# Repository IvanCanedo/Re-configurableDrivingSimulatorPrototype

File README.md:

# Re-configurableDrivingSimulatorPrototype
All files for a Re-configurable Driving Simulator Prototype

Requirements:

Windows 10 20H2

Solidworks Premium 2019 SP4.0

MATLAB 2018b 9.5.0.944444

LabVIEW 2019 19.0f2

KiCad 5.1.10

-To run MATLAB/Simulink simulation-

First open and run

/MATLAB/cinematica_inversa.m

then open and run:

/MATLAB/simulacion/platafomra_esfera.slx

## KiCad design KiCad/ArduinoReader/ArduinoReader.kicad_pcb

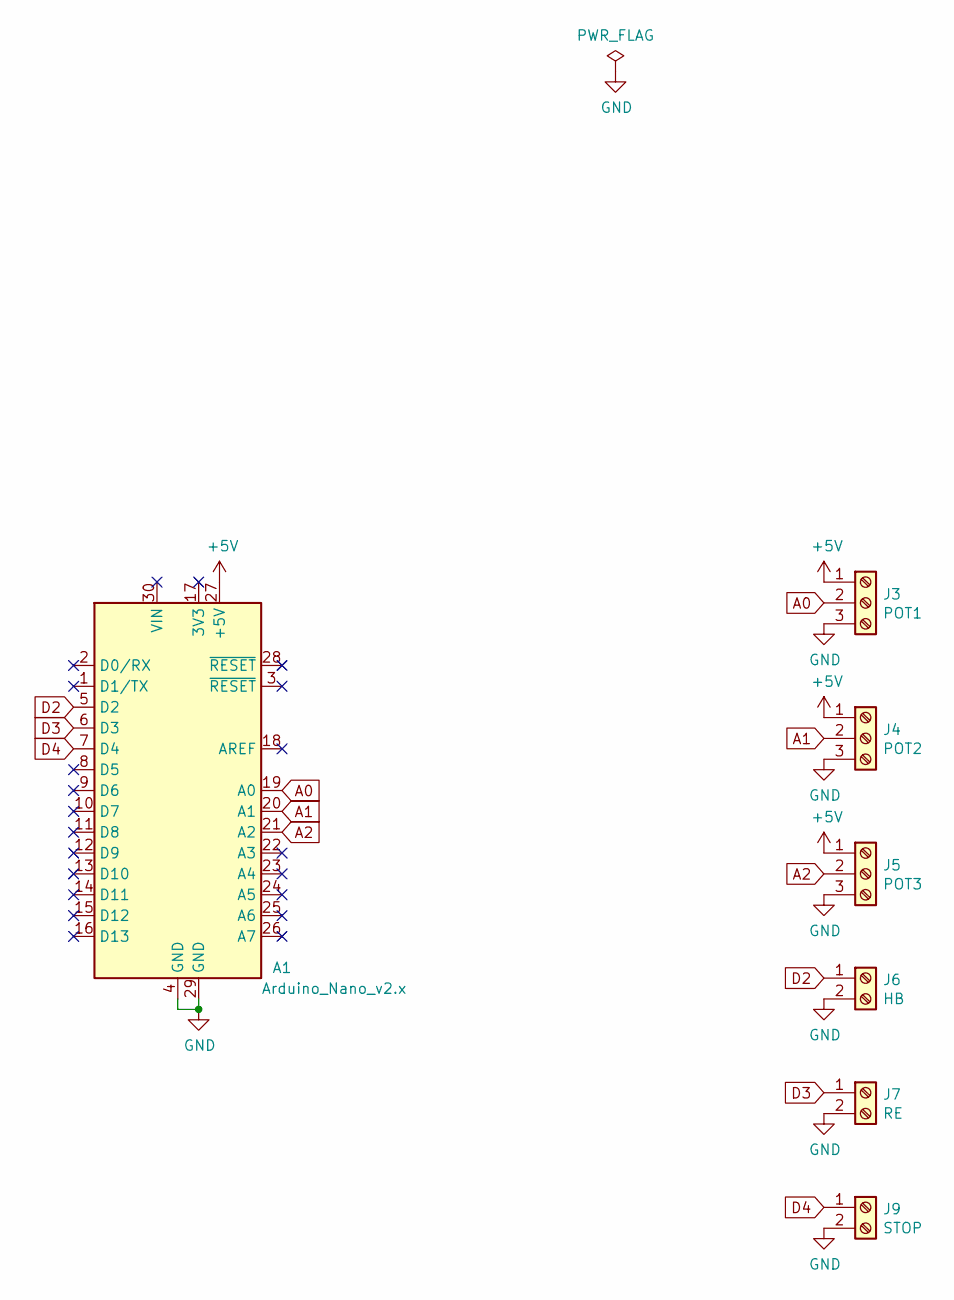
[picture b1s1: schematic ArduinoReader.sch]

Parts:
A1: Arduino_Nano_v2.x; Arduino_Nano
J3: POT1; TerminalBlock_Phoenix_MKDS-1,5-3_1x03_P5.00mm_Horizontal
J4: POT2; TerminalBlock_Phoenix_MKDS-1,5-3_1x03_P5.00mm_Horizontal
J5: POT3; TerminalBlock_Phoenix_MKDS-1,5-3_1x03_P5.00mm_Horizontal
J6: HB; TerminalBlock_Phoenix_MKDS-1,5-2_1x02_P5.00mm_Horizontal
J7: RE; TerminalBlock_Phoenix_MKDS-1,5-2_1x02_P5.00mm_Horizontal
J9: STOP; TerminalBlock_Phoenix_MKDS-1,5-2_1x02_P5.00mm_Horizontal

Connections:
+5V: A1.27 (+5V), J3.1, J4.1, J5.1
A0: A1.19 (A0), J3.2
A1: A1.20 (A1), J4.2
A2: A1.21 (A2), J5.2
D2: A1.5 (D2), J6.1
D3: A1.6 (D3), J7.1
D4: A1.7 (D4), J9.1
GND: A1.4 (GND), A1.29 (GND), J3.3, J4.3, J5.3, J6.2, J7.2, J9.2

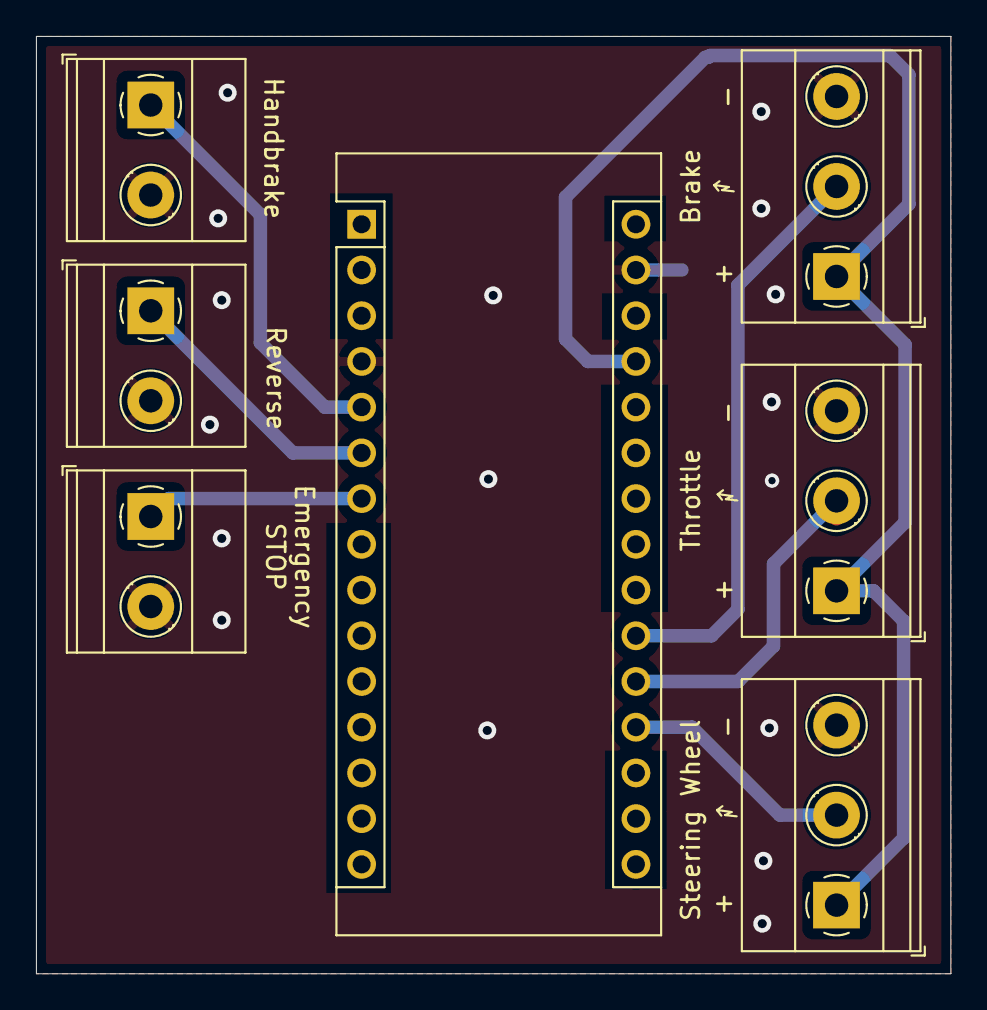
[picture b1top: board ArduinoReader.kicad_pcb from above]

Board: 2 copper layers, 50.8 x 52.1 mm, 7 parts (0 on the bottom side), 8 nets.

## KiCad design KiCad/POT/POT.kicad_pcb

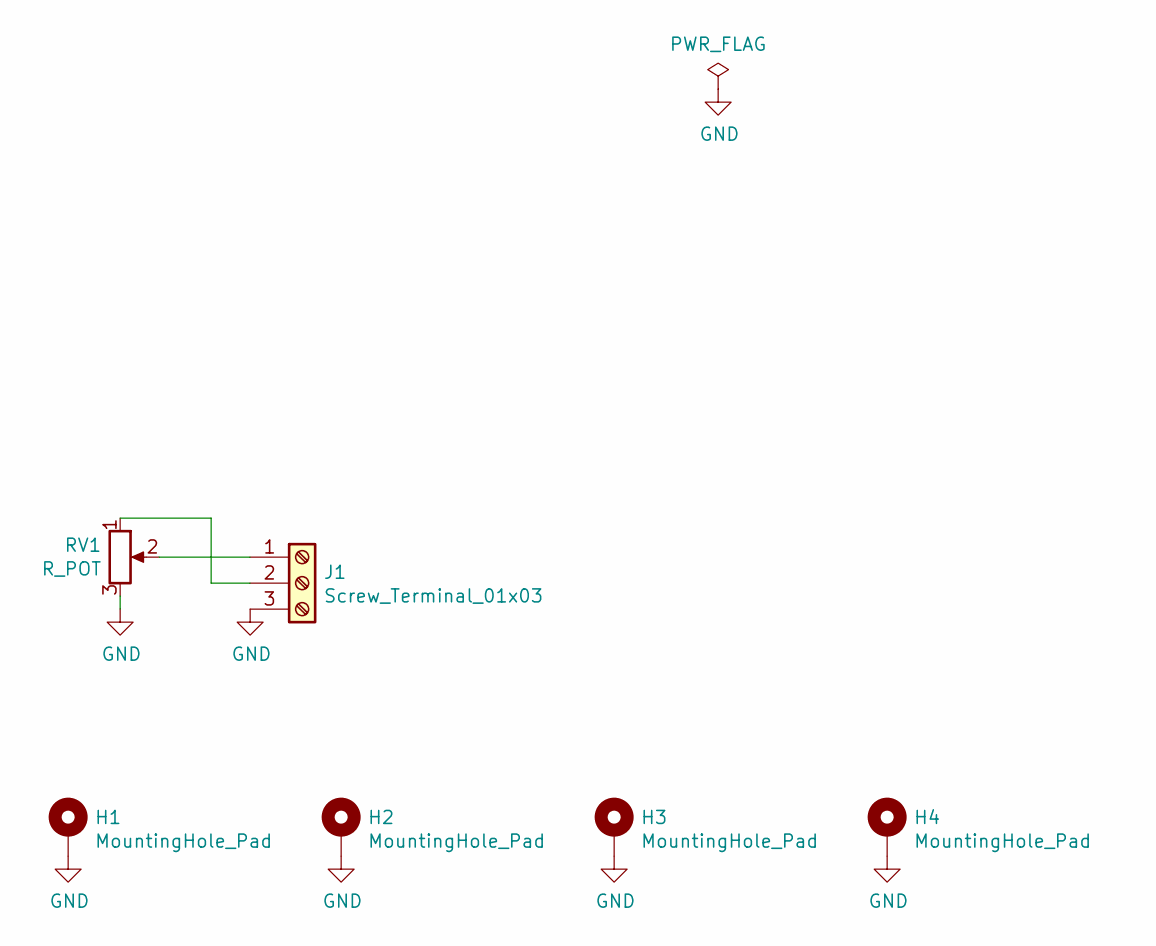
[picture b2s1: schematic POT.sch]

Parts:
H1, H2, H3, H4: MountingHole_Pad; MountingHole_3.2mm_M3_Pad_Via
J1: Screw_Terminal_01x03; TerminalBlock_Phoenix_MKDS-1,5-3-5.08_1x03_P5.08mm_Horizont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
RV1: R_POT; POT3600

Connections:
GND: H1.1, H2.1, H3.1, H4.1, J1.3, RV1.3
unnamed: J1.1, RV1.2
unnamed: J1.2, RV1.1

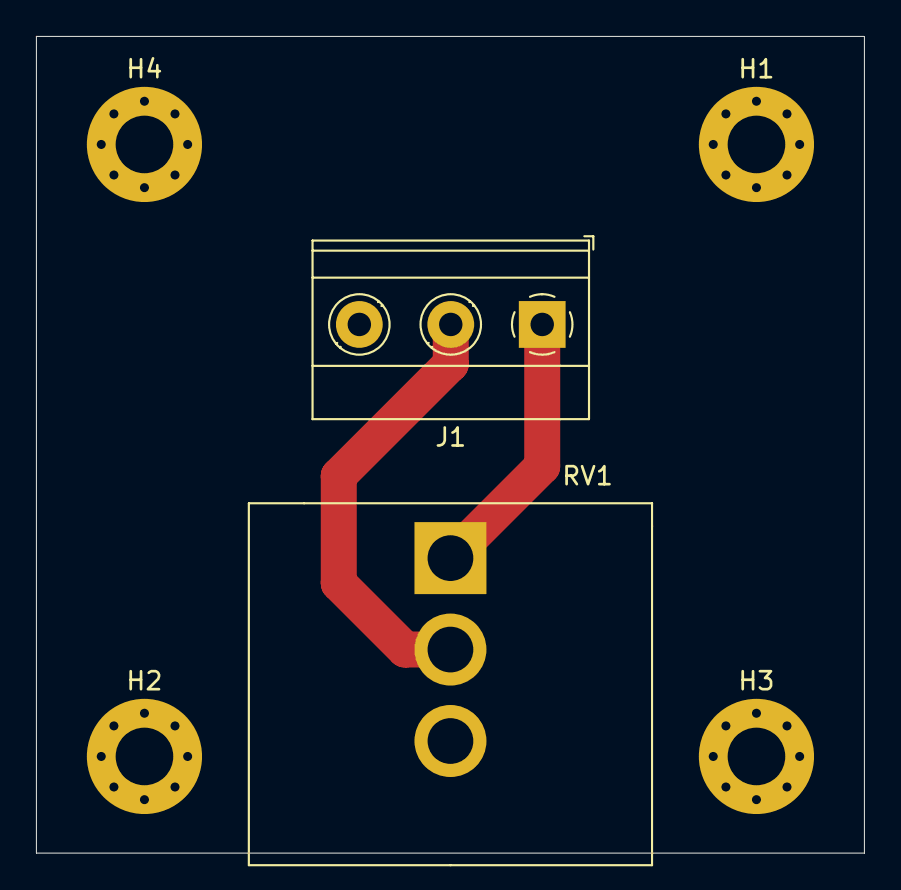
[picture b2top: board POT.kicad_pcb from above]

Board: 2 copper layers, 46.0 x 45.4 mm, 6 parts (0 on the bottom side), 3 nets.

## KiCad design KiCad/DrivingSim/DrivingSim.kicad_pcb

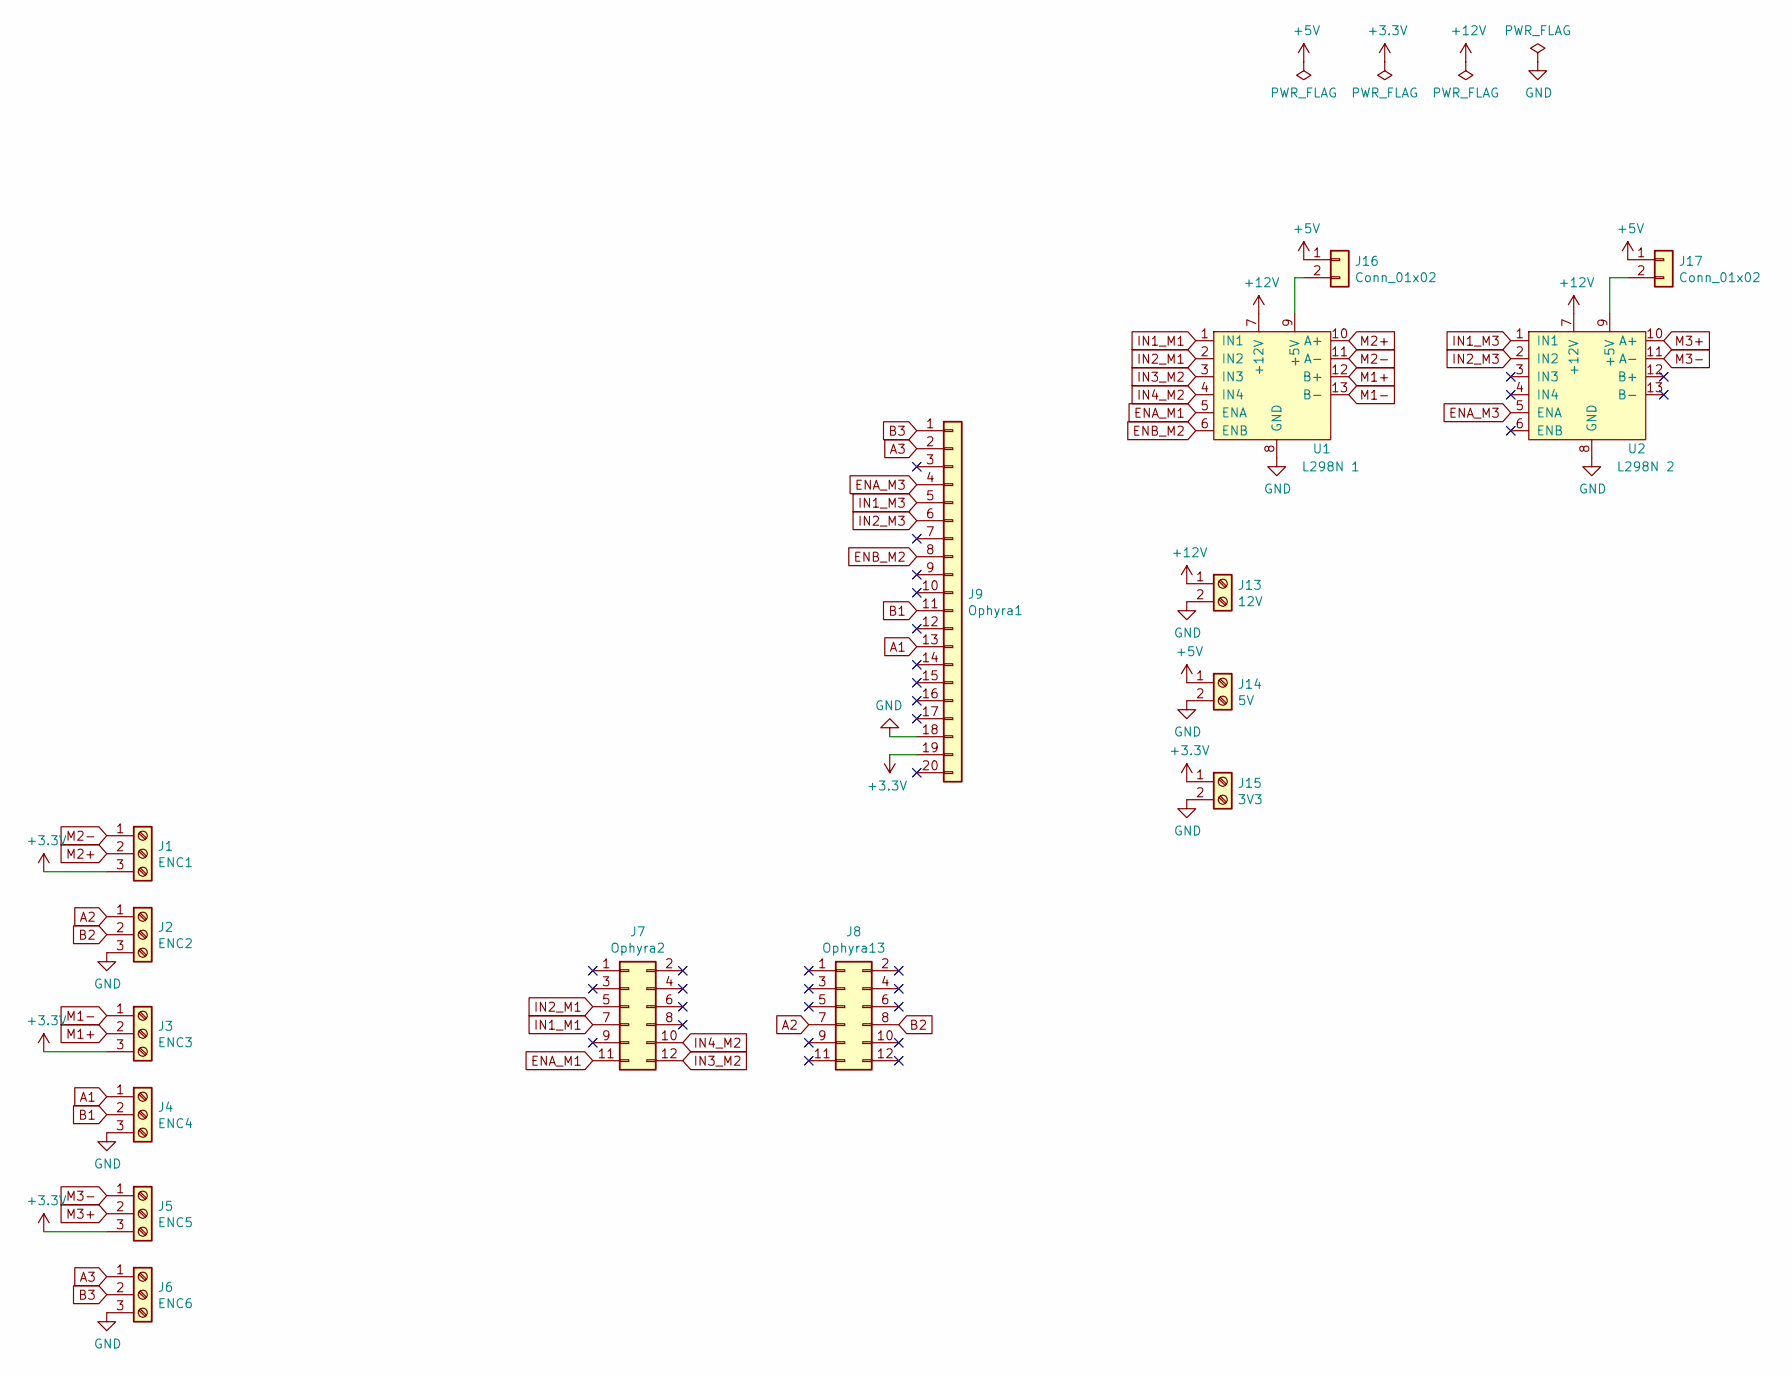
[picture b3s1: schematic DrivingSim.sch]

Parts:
J1: ENC1; TerminalBlock_Phoenix_MKDS-1,5-3-5.08_1x03_P5.08mm_Horizont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
J2: ENC2; TerminalBlock_Phoenix_MKDS-1,5-3-5.08_1x03_P5.08mm_Horizont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
J3: ENC3; TerminalBlock_Phoenix_MKDS-1,5-3-5.08_1x03_P5.08mm_Horizont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
J4: ENC4; TerminalBlock_Phoenix_MKDS-1,5-3-5.08_1x03_P5.08mm_Horizont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
J5: ENC5; TerminalBlock_Phoenix_MKDS-1,5-3-5.08_1x03_P5.08mm_Horizont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
J6: ENC6; TerminalBlock_Phoenix_MKDS-1,5-3-5.08_1x03_P5.08mm_Horizont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
J7: Ophyra2; PinHeader_2x06_P2.54mm_Vertical
J8: Ophyra13; PinHeader_2x06_P2.54mm_Vertical
J9: Ophyra1; PinSocket_1x20_P2.54mm_Vertical
J13: 12V; TerminalBlock_Phoenix_MKDS-1,5-2-5.08_1x02_P5.08mm_Horizont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
J14: 5V; TerminalBlock_Phoenix_MKDS-1,5-2-5.08_1x02_P5.08mm_Horizont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
J15: 3V3; TerminalBlock_Phoenix_MKDS-1,5-2-5.08_1x02_P5.08mm_Horizont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
J16, J17: Conn_01x02; PinHeader_1x02_P2.54mm_Vertical
U1: L298N 1; L298N
U2: L298N 2; L298N

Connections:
+3V3: J1.3, J3.3, J5.3, J9.19, J15.1
+5V: J14.1, J16.1, J17.1
+12V: J13.1, U1.7 (+12V), U2.7 (+12V)
A1: J4.1, J9.13
A2: J2.1, J8.7
A3: J6.1, J9.2
B1: J4.2, J9.11
B2: J2.2, J8.8
B3: J6.2, J9.1
ENA_M1: J7.11, U1.5 (ENA)
ENA_M3: J9.4, U2.5 (ENA)
ENB_M2: J9.8, U1.6 (ENB)
GND: J2.3, J4.3, J6.3, J9.18, J13.2, J14.2, J15.2, U1.8 (GND), U2.8 (GND)
IN1_M1: J7.7, U1.1 (IN1)
IN1_M3: J9.5, U2.1 (IN1)
IN2_M1: J7.5, U1.2 (IN2)
IN2_M3: J9.6, U2.2 (IN2)
IN3_M2: J7.12, U1.3 (IN3)
IN4_M2: J7.10, U1.4 (IN4)
M1+: J3.2, U1.12 (B+)
M1-: J3.1, U1.13 (B-)
M2+: J1.2, U1.10 (A+)
M2-: J1.1, U1.11 (A-)
M3+: J5.2, U2.10 (A+)
M3-: J5.1, U2.11 (A-)
unnamed: J16.2, U1.9 (+5V)
unnamed: J17.2, U2.9 (+5V)

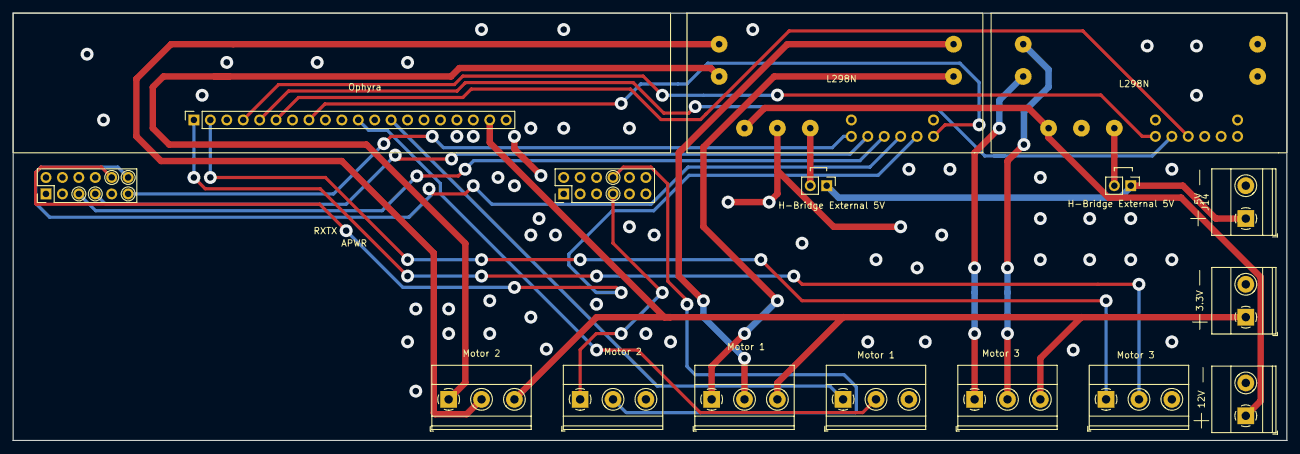
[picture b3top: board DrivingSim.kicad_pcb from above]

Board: 2 copper layers, 196.9 x 66.0 mm, 16 parts (0 on the bottom side), 27 nets.

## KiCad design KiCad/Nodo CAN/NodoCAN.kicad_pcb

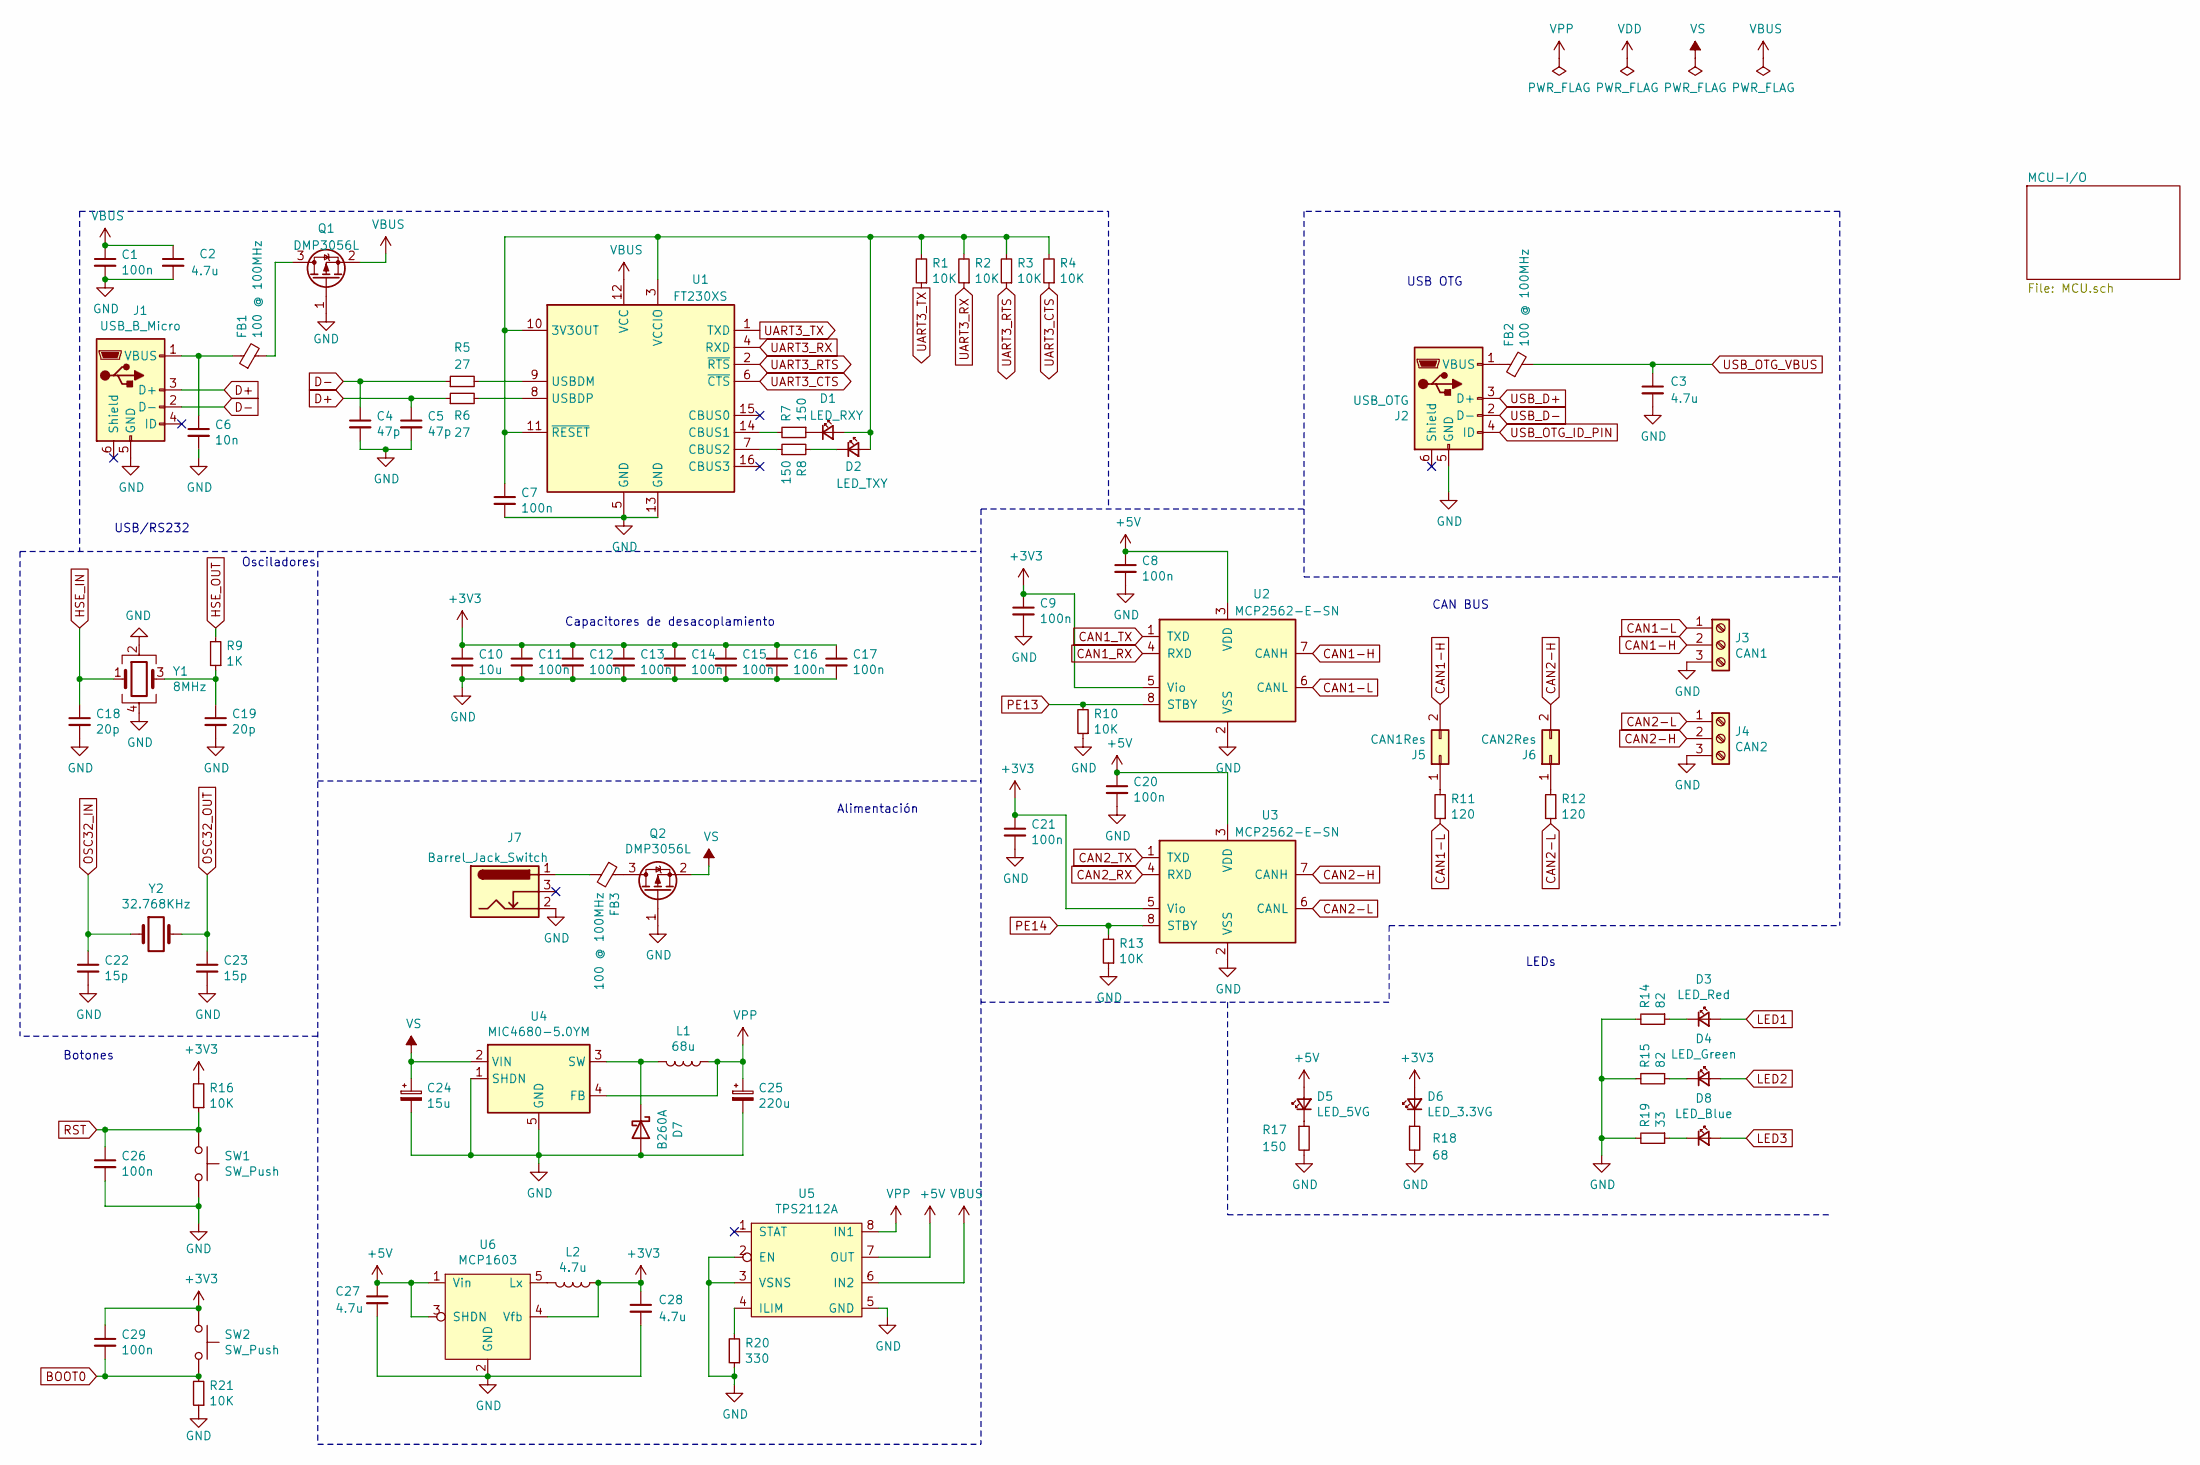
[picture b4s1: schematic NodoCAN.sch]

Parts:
C1, C7, C8, C9, C20, C21, C26, C29: 100n; C_0603_1608Metric
C2, C3, C27, C28: 4.7u; C_0805_2012Metric
C4, C5: 47p; C_0603_1608Metric
C6: 10n; C_0603_1608Metric
C10: 10u; C_0603_1608Metric
C11, C12, C13, C14, C15, C16, C17: 100n; C_0402_1005Metric
C18, C19: 20p; C_0402_1005Metric
C22, C23: 15p; C_0402_1005Metric
C24: 15u; CP_Elec_5x5.3
C25: 220u; CP_Elec_6.3x9.9
D1: LED_RXY; LED_0805_2012Metric
D2: LED_TXY; LED_0805_2012Metric
D3: LED_Red; LED_PLCC-2
D4: LED_Green; LED_PLCC-2
D5: LED_5VG; LED_0805_2012Metric
D6: LED_3.3VG; LED_0805_2012Metric
D7: B260A; D_SMA
D8: LED_Blue; LED_PLCC-2
FB1, FB2, FB3: 100 @ 100MHz; L_0805_2012Metric
J1: USB_B_Micro; USB_Micro-B_GCT_USB3076-30-A
J2: USB_OTG; USB_Micro-B_GCT_USB3076-30-A
J3: CAN1; TerminalBlock_Phoenix_MKDS-1,5-3-5.08_1x03_P5.08mm_Horizont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
J4: CAN2; TerminalBlock_Phoenix_MKDS-1,5-3-5.08_1x03_P5.08mm_Horizont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
J5: CAN1Res; PinHeader_2x01_P2.54mm_Vertical
J6: CAN2Res; PinHeader_2x01_P2.54mm_Vertical
J7: Barrel_Jack_Switch; BarrelJack_Horizontal
L1: 68u; UPB2
L2: 4.7u; L_1210_3225Metric
Q1, Q2: DMP3056L; SOT-23
R1, R2, R3, R4, R10, R13, R16, R21: 10K; R_0603_1608Metric
R5, R6: 27; R_0402_1005Metric
R7, R8, R17: 150; R_0805_2012Metric
R9: 1K; R_0402_1005Metric
R11, R12: 120; R_0805_2012Metric
R14, R15: 82; R_0805_2012Metric
R18: 68; R_0805_2012Metric
R19: 33; R_0805_2012Metric
R20: 330; R_1206_3216Metric
SW1, SW2: SW_Push; SW_Push_1P1T_NO_6x6mm_H9.5mm
U1: FT230XS; SSOP-16_3.9x4.9mm_P0.635mm
U2, U3: MCP2562-E-SN; SOIC-8_3.9x4.9mm_P1.27mm
U4: MIC4680-5.0YM; SOIC-8_3.9x4.9mm_P1.27mm
U5: TPS2112A; TSSOP-8_4.4x3mm_P0.65mm
U6: MCP1603; TSOT-23-5
Y1: 8MHz; Crystal_SMD_Abracon_ABM3B-4Pin_5.0x3.2mm
Y2: 32.768KHz; Crystal_SMD_2012-2Pin_2.0x1.2mm

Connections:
+3V3: C9.1, C10.1, C11.1, C12.1, C13.1, C14.1, C15.1, C16.1, C17.1, C21.1, C28.1, C29.1, D6.2 (A), L2.1, R16.2, SW2.1, U2.5 (Vio), U3.5 (Vio), U6.4 (Vfb); also elsewhere on the board
+5V: C8.1, C20.1, C27.1, D5.2 (A), U2.3 (VDD), U3.3 (VDD), U5.7 (OUT), U6.1 (Vin), U6.3 (SHDN); also elsewhere on the board
BOOT0: C29.2, R21.2, SW2.2; also elsewhere on the board
CAN1-H: J3.2, J5.2, U2.7 (CANH)
CAN1-L: J3.1, R11.1, U2.6 (CANL)
CAN1_RX: U2.4 (RXD); also elsewhere on the board
CAN1_TX: U2.1 (TXD); also elsewhere on the board
CAN2-H: J4.2, J6.2, U3.7 (CANH)
CAN2-L: J4.1, R12.1, U3.6 (CANL)
CAN2_RX: U3.4 (RXD); also elsewhere on the board
CAN2_TX: U3.1 (TXD); also elsewhere on the board
D+: C5.1, J1.3 (D+), R6.1
D-: C4.1, J1.2 (D-), R5.1
GND: C1.2, C2.2, C3.2, C4.2, C5.2, C6.2, C7.2, C8.2, C9.2, C10.2, C11.2, C12.2, C13.2, C14.2, C15.2, C16.2, C17.2, C18.2, C19.2, C20.2, C21.2, C22.2, C23.2, C24.2, C25.2, C26.2, C27.2, C28.2, D7.2 (A), J1.5 (GND), J2.5 (GND), J3.3, J4.3, J7.2, Q1.1 (G), Q2.1 (G), R10.1, R13.1, R14.2, R15.2, R17.2, R18.2, R19.2, R20.1, R21.1, SW1.2, U1.5 (GND), U1.13 (GND), U2.2 (VSS), U3.2 (VSS), U4.1 (SHDN), U4.5 (GND), U4.6 (GND), U4.7 (GND), U4.8 (GND), U5.2 (EN), U5.3 (VSNS), U5.5 (GND), U6.2 (GND), Y1.2, Y1.4; also elsewhere on the board
HSE_IN: C18.1, Y1.1; also elsewhere on the board
HSE_OUT: R9.2; also elsewhere on the board
LED1: D3.2 (A); also elsewhere on the board
LED2: D4.2 (A); also elsewhere on the board
LED3: D8.2 (A); also elsewhere on the board
unnamed: C6.1, FB1.1, J1.1 (VBUS)
unnamed: C7.1, D1.2 (A), D2.2 (A), R1.2, R2.2, R3.2, R4.2, U1.3 (VCCIO), U1.10 (3V3OUT), U1.11 (~RESET)
unnamed: C19.1, R9.1, Y1.3
unnamed: D1.1 (K), R7.1
unnamed: D2.1 (K), R8.2
unnamed: D3.1 (K), R14.1
unnamed: D4.1 (K), R15.1
unnamed: D5.1 (K), R17.1
unnamed: D6.1 (K), R18.1
unnamed: D7.1 (K), L1.2, U4.3 (SW)
unnamed: D8.1 (K), R19.1
unnamed: FB1.2, Q1.3 (D)
unnamed: FB2.1, J2.1 (VBUS)
unnamed: FB3.1, Q2.3 (D)
unnamed: FB3.2, J7.1
unnamed: J5.1, R11.2
unnamed: J6.1, R12.2
unnamed: L2.2, U6.5 (Lx)
unnamed: R5.2, U1.9 (USBDM)
unnamed: R6.2, U1.8 (USBDP)
unnamed: R7.2, U1.14 (CBUS1)
unnamed: R8.1, U1.7 (CBUS2)
unnamed: R20.2, U5.4 (ILIM)
OSC32_IN: C22.1, Y2.1; also elsewhere on the board
OSC32_OUT: C23.1, Y2.2; also elsewhere on the board
PE13: R10.2, U2.8 (STBY); also elsewhere on the board
PE14: R13.2, U3.8 (STBY); also elsewhere on the board
RST: C26.1, R16.1, SW1.1; also elsewhere on the board
UART3_CTS: R4.1, U1.6 (~CTS); also elsewhere on the board
UART3_RTS: R3.1, U1.2 (~RTS); also elsewhere on the board
UART3_RX: R2.1, U1.4 (RXD); also elsewhere on the board
UART3_TX: R1.1, U1.1 (TXD); also elsewhere on the board
USB_D+: J2.3 (D+); also elsewhere on the board
USB_D-: J2.2 (D-); also elsewhere on the board
USB_OTG_ID_PIN: J2.4 (ID); also elsewhere on the board
USB_OTG_VBUS: C3.1, FB2.2; also elsewhere on the board
VBUS: C1.1, C2.1, Q1.2 (S), U1.12 (VCC), U5.6 (IN2); also elsewhere on the board
VPP: C25.1, L1.1, U4.4 (FB), U5.8 (IN1)
VS: C24.1, Q2.2 (S), U4.2 (VIN); also elsewhere on the board

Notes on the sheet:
CAN BUS
USB OTG
Alimentación
Capacitores de desacoplamiento
LEDs
Botones
Osciladores
USB/RS232

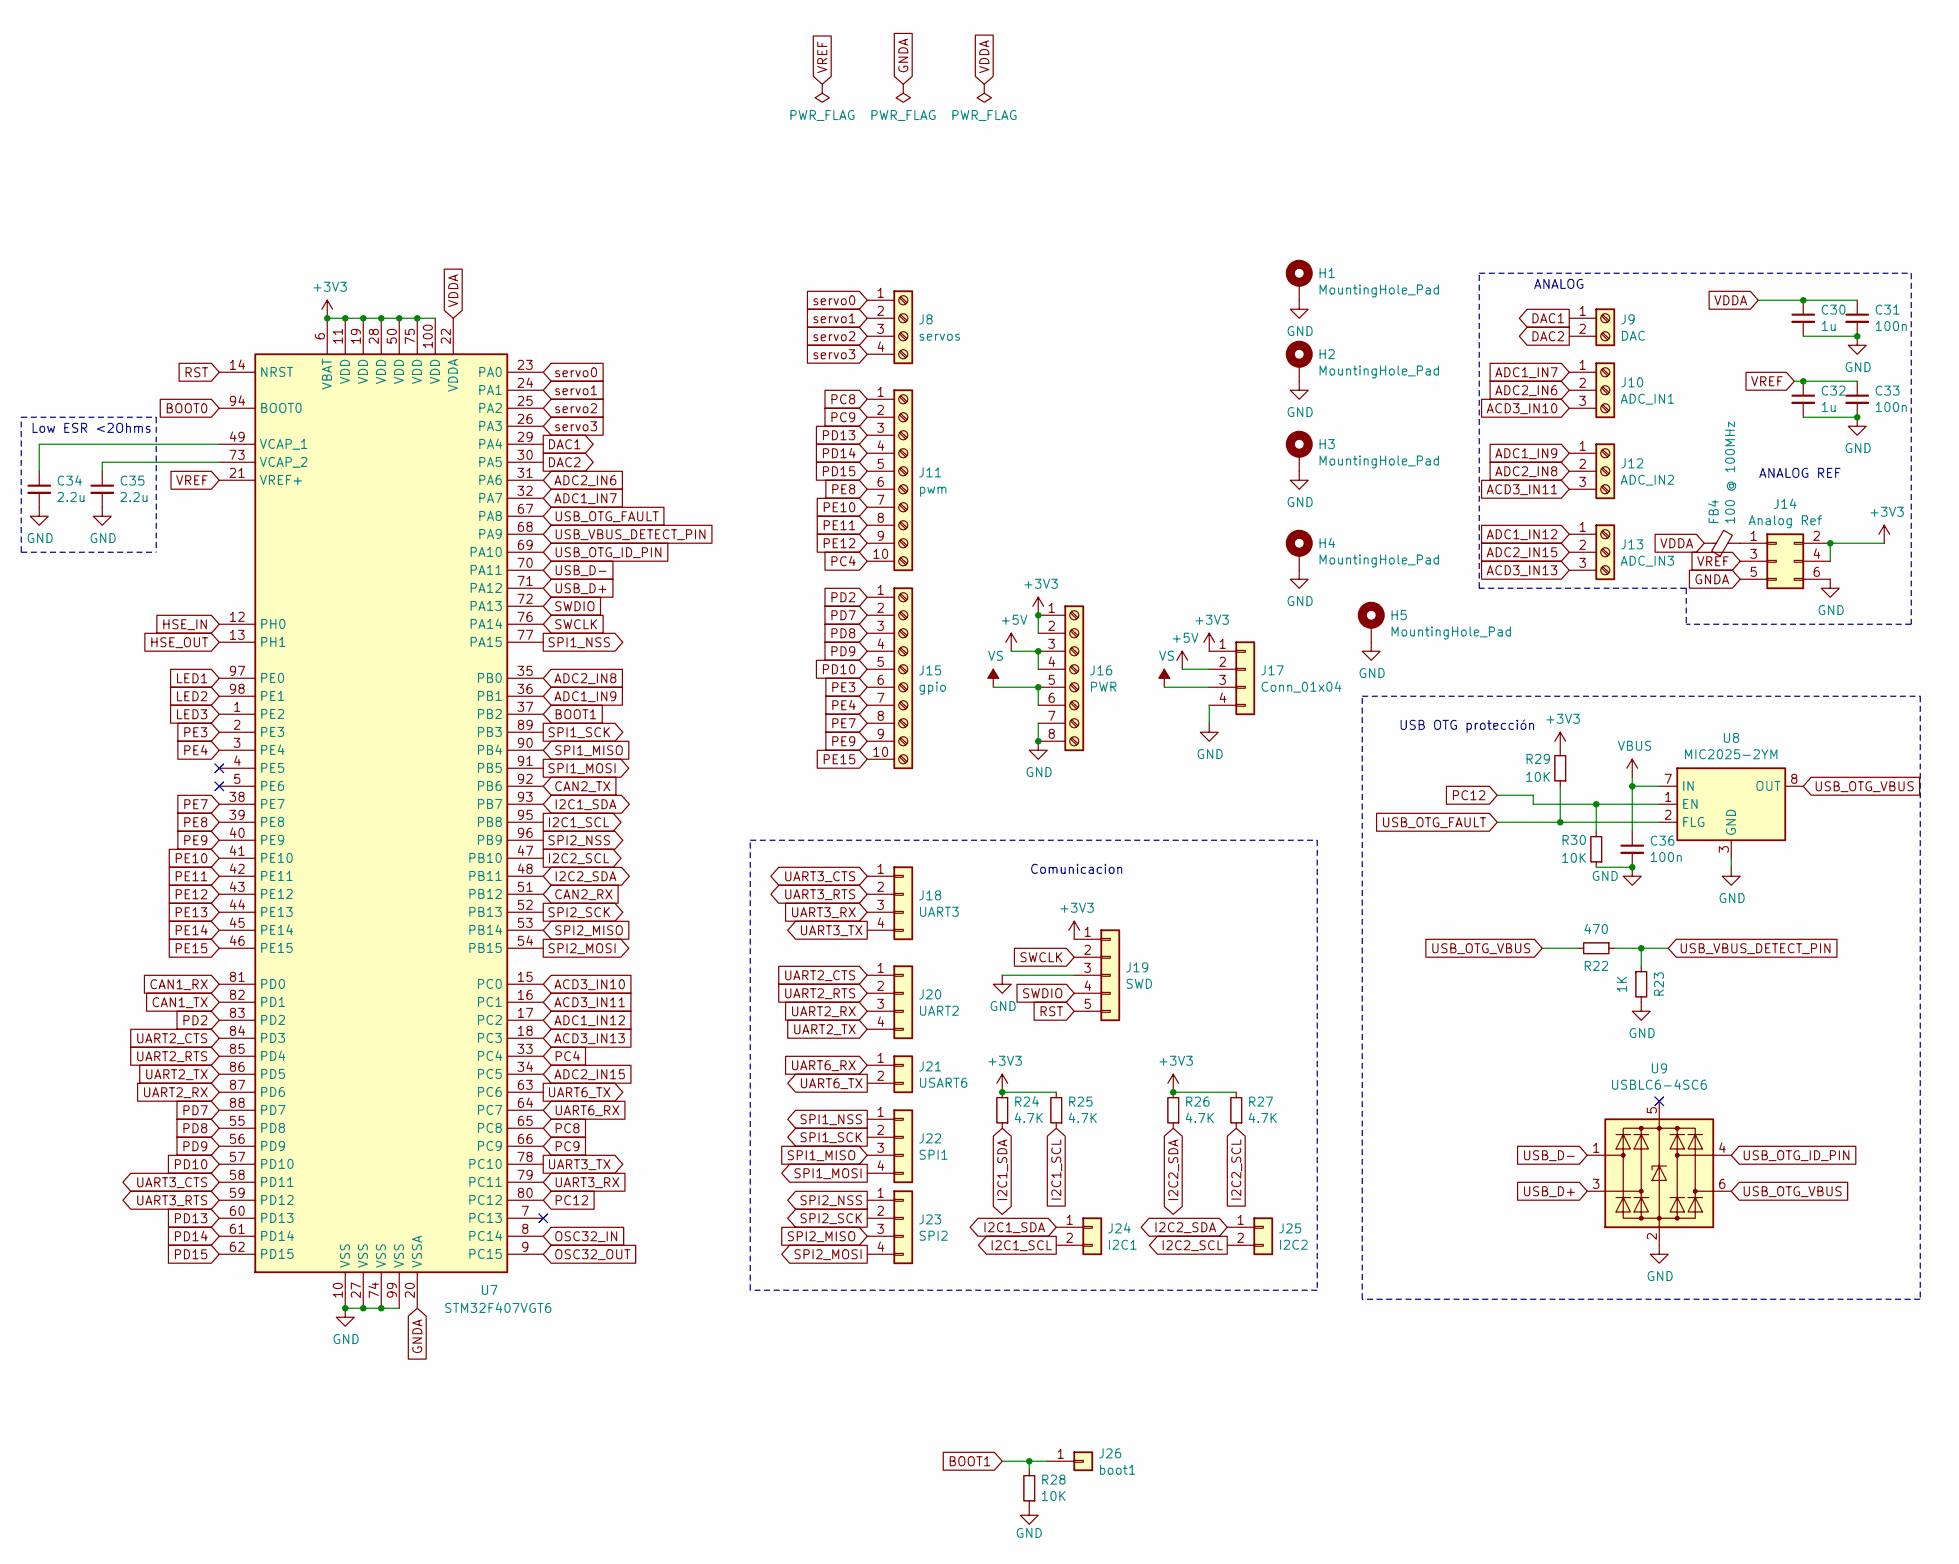
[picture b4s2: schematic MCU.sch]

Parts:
C30, C32: 1u; C_0402_1005Metric
C31, C33: 100n; C_0402_1005Metric
C34, C35: 2.2u; C_0805_2012Metric
C36: 100n; C_0603_1608Metric
FB4: 100 @ 100MHz; L_0805_2012Metric
H1, H2, H3, H4, H5: MountingHole_Pad; MountingHole_4.3mm_M4_Pad_Via
J8: servos; TerminalBlock_Phoenix_MKDS-1,5-4-5.08_1x04_P5.08mm_Horizont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
J9: DAC; TerminalBlock_Phoenix_MKDS-1,5-2-5.08_1x02_P5.08mm_Horizont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
J10: ADC_IN1; TerminalBlock_Phoenix_MKDS-1,5-3-5.08_1x03_P5.08mm_Horizont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
J11: pwm; TerminalBlock_Phoenix_MKDS-1,5-10-5.08_1x10_P5.08mm_Horizon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
J12: ADC_IN2; TerminalBlock_Phoenix_MKDS-1,5-3-5.08_1x03_P5.08mm_Horizont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
J13: ADC_IN3; TerminalBlock_Phoenix_MKDS-1,5-3-5.08_1x03_P5.08mm_Horizont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
J14: Analog Ref; PinHeader_2x03_P2.54mm_Vertical
J15: gpio; TerminalBlock_Phoenix_MKDS-1,5-10-5.08_1x10_P5.08mm_Horizon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
J16: PWR; TerminalBlock_Phoenix_MKDS-1,5-8-5.08_1x08_P5.08mm_Horizont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
J17: Conn_01x04; PinHeader_1x04_P2.54mm_Vertical
J18: UART3; PinHeader_1x04_P2.54mm_Vertical
J19: SWD; PinHeader_1x05_P2.54mm_Vertical
J20: UART2; PinHeader_1x04_P2.54mm_Vertical
J21: USART6; PinHeader_1x02_P2.54mm_Vertical
J22: SPI1; PinHeader_1x04_P2.54mm_Vertical
J23: SPI2; PinHeader_1x04_P2.54mm_Vertical
J24: I2C1; PinHeader_1x02_P2.54mm_Vertical
J25: I2C2; PinHeader_1x02_P2.54mm_Vertical
J26: boot1; PinHeader_1x01_P2.54mm_Vertical
R22: 470; R_0805_2012Metric
R23: 1K; R_0805_2012Metric
R24, R25, R26, R27: 4.7K; R_0402_1005Metric
R28, R29, R30: 10K; R_0603_1608Metric
U7: STM32F407VGT6; LQFP-100_14x14mm_P0.5mm
U8: MIC2025-2YM; SOIC-8_3.9x4.9mm_P1.27mm
U9: USBLC6-4SC6; SOT-23-6

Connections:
+3V3: J14.2, J14.4, J16.1, J16.2, J17.1, J19.1, R24.2, R25.2, R26.2, R27.2, R29.2, U7.6 (VBAT), U7.11 (VDD), U7.19 (VDD), U7.28 (VDD), U7.50 (VDD), U7.75 (VDD), U7.100 (VDD); also elsewhere on the board
+5V: J16.3, J16.4, J17.2; also elsewhere on the board
ACD3_IN10: J10.3, U7.15 (PC0)
ACD3_IN11: J12.3, U7.16 (PC1)
ACD3_IN13: J13.3, U7.18 (PC3)
ADC1_IN7: J10.1, U7.32 (PA7)
ADC1_IN9: J12.1, U7.36 (PB1)
ADC1_IN12: J13.1, U7.17 (PC2)
ADC2_IN6: J10.2, U7.31 (PA6)
ADC2_IN8: J12.2, U7.35 (PB0)
ADC2_IN15: J13.2, U7.34 (PC5)
BOOT0: U7.94 (BOOT0); also elsewhere on the board
BOOT1: J26.1, R28.2, U7.37 (PB2)
CAN1_RX: U7.81 (PD0); also elsewhere on the board
CAN1_TX: U7.82 (PD1); also elsewhere on the board
CAN2_RX: U7.51 (PB12); also elsewhere on the board
CAN2_TX: U7.92 (PB6); also elsewhere on the board
DAC1: J9.1, U7.29 (PA4)
DAC2: J9.2, U7.30 (PA5)
GND: C30.2, C31.2, C32.2, C33.2, C34.2, C35.2, C36.2, H1.1, H2.1, H3.1, H4.1, H5.1, J14.6, J16.7, J16.8, J17.4, J19.3, R23.2, R28.1, R30.1, U7.10 (VSS), U7.27 (VSS), U7.74 (VSS), U7.99 (VSS), U8.3 (GND), U9.2 (GND); also elsewhere on the board
GNDA: J14.5, U7.20 (VSSA)
HSE_IN: U7.12 (PH0); also elsewhere on the board
HSE_OUT: U7.13 (PH1); also elsewhere on the board
I2C1_SCL: J24.2, R25.1, U7.95 (PB8)
I2C1_SDA: J24.1, R24.1, U7.93 (PB7)
I2C2_SCL: J25.2, R27.1, U7.47 (PB10)
I2C2_SDA: J25.1, R26.1, U7.48 (PB11)
LED1: U7.97 (PE0); also elsewhere on the board
LED2: U7.98 (PE1); also elsewhere on the board
LED3: U7.1 (PE2); also elsewhere on the board
unnamed: C34.1, U7.49 (VCAP_1)
unnamed: C35.1, U7.73 (VCAP_2)
unnamed: FB4.2, J14.1
OSC32_IN: U7.8 (PC14); also elsewhere on the board
OSC32_OUT: U7.9 (PC15); also elsewhere on the board
PC4: J11.10, U7.33 (PC4)
PC8: J11.1, U7.65 (PC8)
PC9: J11.2, U7.66 (PC9)
PC12: R30.2, U7.80 (PC12), U8.1 (EN)
PD2: J15.1, U7.83 (PD2)
PD7: J15.2, U7.88 (PD7)
PD8: J15.3, U7.55 (PD8)
PD9: J15.4, U7.56 (PD9)
PD10: J15.5, U7.57 (PD10)
PD13: J11.3, U7.60 (PD13)
PD14: J11.4, U7.61 (PD14)
PD15: J11.5, U7.62 (PD15)
PE3: J15.6, U7.2 (PE3)
PE4: J15.7, U7.3 (PE4)
PE7: J15.8, U7.38 (PE7)
PE8: J11.6, U7.39 (PE8)
PE9: J15.9, U7.40 (PE9)
PE10: J11.7, U7.41 (PE10)
PE11: J11.8, U7.42 (PE11)
PE12: J11.9, U7.43 (PE12)
PE13: U7.44 (PE13); also elsewhere on the board
PE14: U7.45 (PE14); also elsewhere on the board
PE15: J15.10, U7.46 (PE15)
RST: J19.5, U7.14 (NRST); also elsewhere on the board
SPI1_MISO: J22.3, U7.90 (PB4)
SPI1_MOSI: J22.4, U7.91 (PB5)
SPI1_NSS: J22.1, U7.77 (PA15)
SPI1_SCK: J22.2, U7.89 (PB3)
SPI2_MISO: J23.3, U7.53 (PB14)
SPI2_MOSI: J23.4, U7.54 (PB15)
SPI2_NSS: J23.1, U7.96 (PB9)
SPI2_SCK: J23.2, U7.52 (PB13)
SWCLK: J19.2, U7.76 (PA14)
SWDIO: J19.4, U7.72 (PA13)
UART2_CTS: J20.1, U7.84 (PD3)
UART2_RTS: J20.2, U7.85 (PD4)
UART2_RX: J20.3, U7.87 (PD6)
UART2_TX: J20.4, U7.86 (PD5)
UART3_CTS: J18.1, U7.58 (PD11); also elsewhere on the board
UART3_RTS: J18.2, U7.59 (PD12); also elsewhere on the board
UART3_RX: J18.3, U7.79 (PC11); also elsewhere on the board
UART3_TX: J18.4, U7.78 (PC10); also elsewhere on the board
UART6_RX: J21.1, U7.64 (PC7)
UART6_TX: J21.2, U7.63 (PC6)
USB_D+: U7.71 (PA12), U9.3 (I/O2); also elsewhere on the board
USB_D-: U7.70 (PA11), U9.1 (I/O1); also elsewhere on the board
USB_OTG_FAULT: R29.1, U7.67 (PA8), U8.2 (FLG)
USB_OTG_ID_PIN: U7.69 (PA10), U9.4 (I/O3); also elsewhere on the board
USB_OTG_VBUS: R22.2, U8.6 (OUT), U8.8 (OUT), U9.6 (I/O4); also elsewhere on the board
USB_VBUS_DETECT_PIN: R22.1, R23.1, U7.68 (PA9)
VBUS: C36.1, U8.7 (IN); also elsewhere on the board
VDDA: C30.1, C31.1, FB4.1, U7.22 (VDDA)
VREF: C32.1, C33.1, J14.3, U7.21 (VREF+)
VS: J16.5, J16.6, J17.3; also elsewhere on the board
servo0: J8.1, U7.23 (PA0)
servo1: J8.2, U7.24 (PA1)
servo2: J8.3, U7.25 (PA2)
servo3: J8.4, U7.26 (PA3)

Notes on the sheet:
ANALOG
ANALOG REF
Comunicacion
Low ESR <2Ohms
USB OTG protección

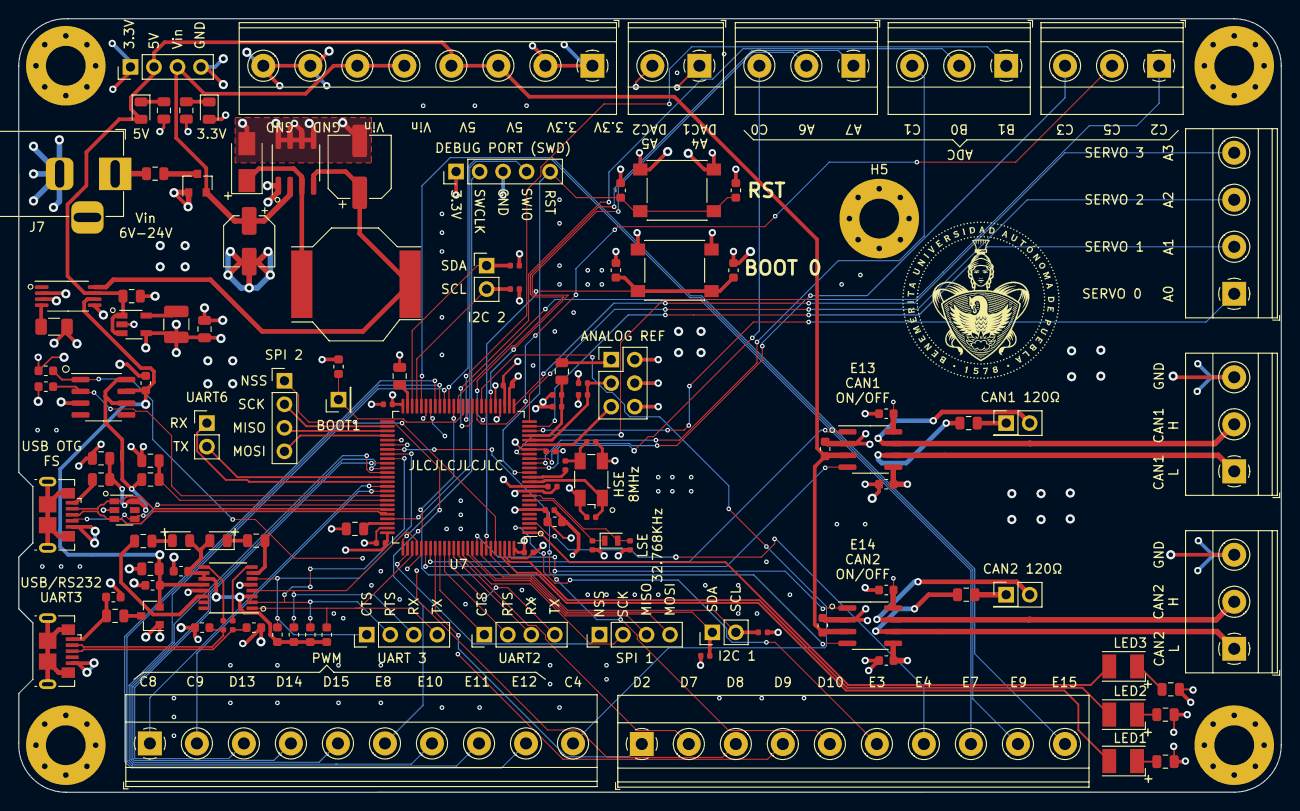
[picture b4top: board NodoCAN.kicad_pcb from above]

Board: 4 copper layers, 136.4 x 83.6 mm, 126 parts (0 on the bottom side), 123 nets.
